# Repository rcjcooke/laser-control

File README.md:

# laser-control
Controller and Wi-fi enabler for Atomstack X20 Pro laser cutter, air assist and air filter

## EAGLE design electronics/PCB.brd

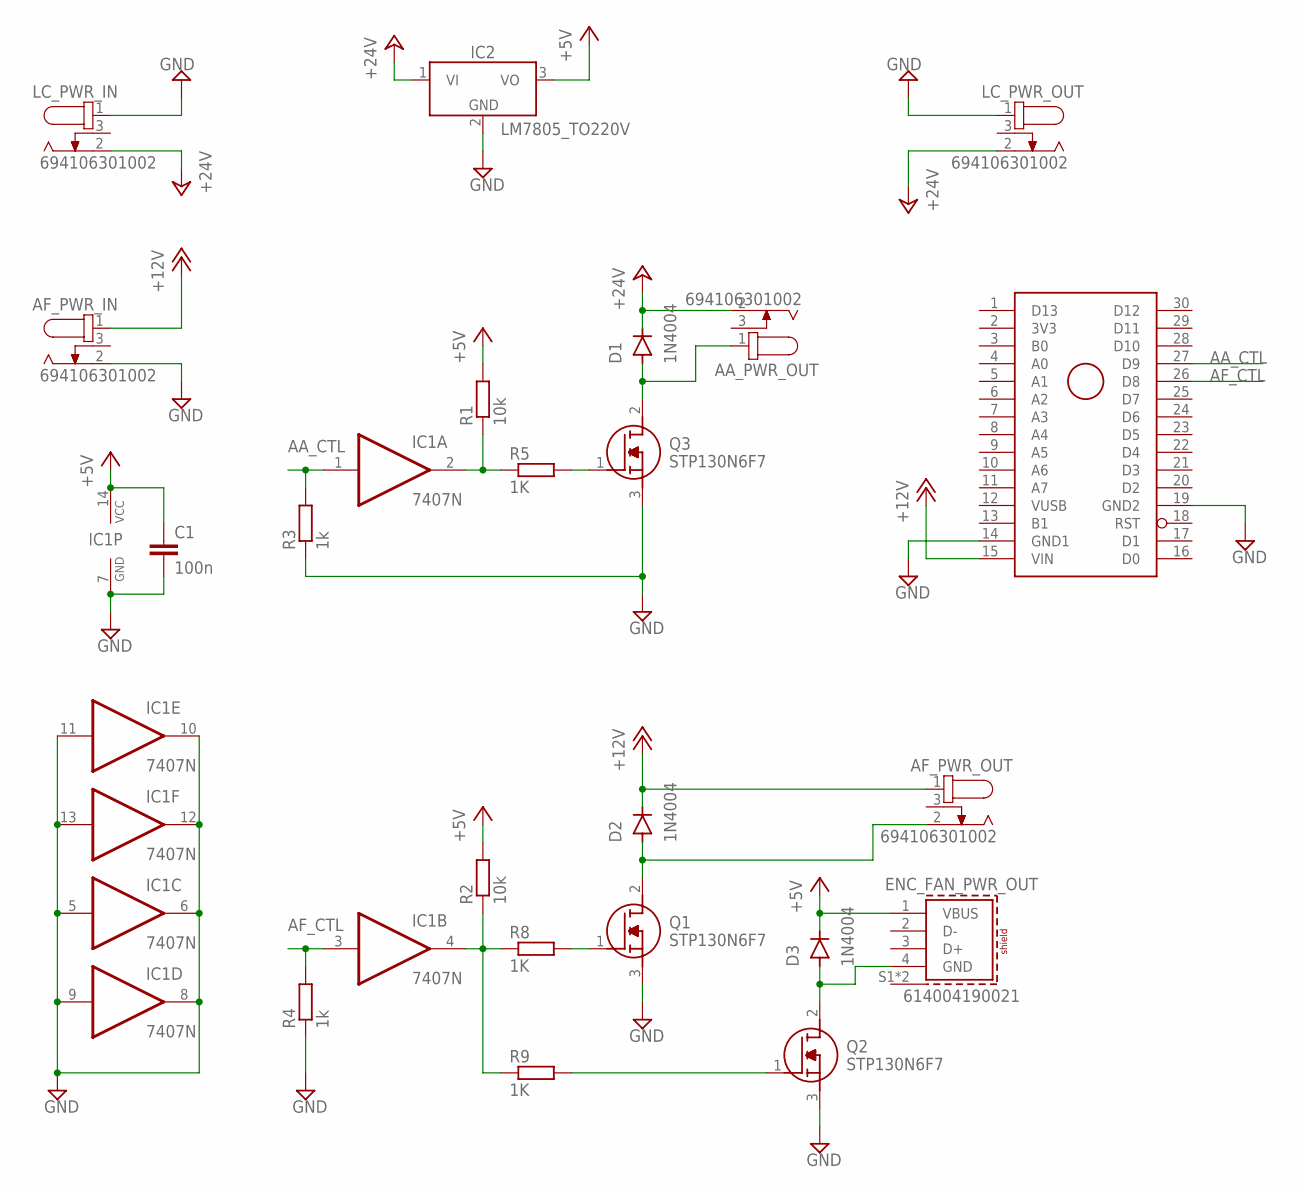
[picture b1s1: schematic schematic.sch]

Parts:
AA_PWR_OUT: 694106301002
AF_PWR_IN: 694106301002
AF_PWR_OUT: 694106301002
C1: 100n; C050-024X044
D1, D2, D3: 1N4004; DO-41
ENC_FAN_PWR_OUT: 614004190021
IC1: 7407N; DIL14
IC2: LM7805_TO220V; TO220V
LC_PWR_IN: 694106301002
LC_PWR_OUT: 694106301002
Q1, Q2, Q3: STP130N6F7; TO255P460X1020X2008-3P
R1, R2: 10k; 0204/7
R3, R4: 1k; 0204/7
R5, R8, R9: 1K; 0204/7
U$1: ARDUINO_NANO_ESP32; ARDUINO_NANO_ESP32_ON_HEADERS

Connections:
+5V: C1.1, D3.C, ENC_FAN_PWR_OUT.1 (VBUS), IC1.14 (VCC), IC2.3 (VO), R1.2, R2.2
+12V: AF_PWR_IN.1, AF_PWR_OUT.1, D2.C, U$1.15 (VIN)
+24V: AA_PWR_OUT.2, D1.C, IC2.1 (VI), LC_PWR_IN.2, LC_PWR_OUT.2
AA_CTL: IC1.1 (I), R3.2, U$1.27 (D9)
AF_CTL: IC1.3 (I), R4.2, U$1.26 (D8)
GND: AF_PWR_IN.2, C1.2, IC1.5 (I), IC1.6 (O), IC1.7 (GND), IC1.8 (O), IC1.9 (I), IC1.10 (O), IC1.11 (I), IC1.12 (O), IC1.13 (I), IC2.2 (GND), LC_PWR_IN.1, LC_PWR_OUT.1, Q1.3 (S), Q2.3 (S), Q3.3 (S), R3.1, R4.1, U$1.14 (GND1), U$1.19 (GND2)
unnamed: AF_PWR_OUT.2, D2.A, Q1.2 (D)
unnamed: Q2.1 (G), R9.2
unnamed: IC1.2 (O), R1.1, R5.1
unnamed: Q1.1 (G), R8.2
unnamed: Q3.1 (G), R5.2
unnamed: D3.A, ENC_FAN_PWR_OUT.4 (GND), Q2.2 (D)
unnamed: IC1.4 (O), R2.1, R8.1, R9.1
unnamed: AA_PWR_OUT.1, D1.A, Q3.2 (D)

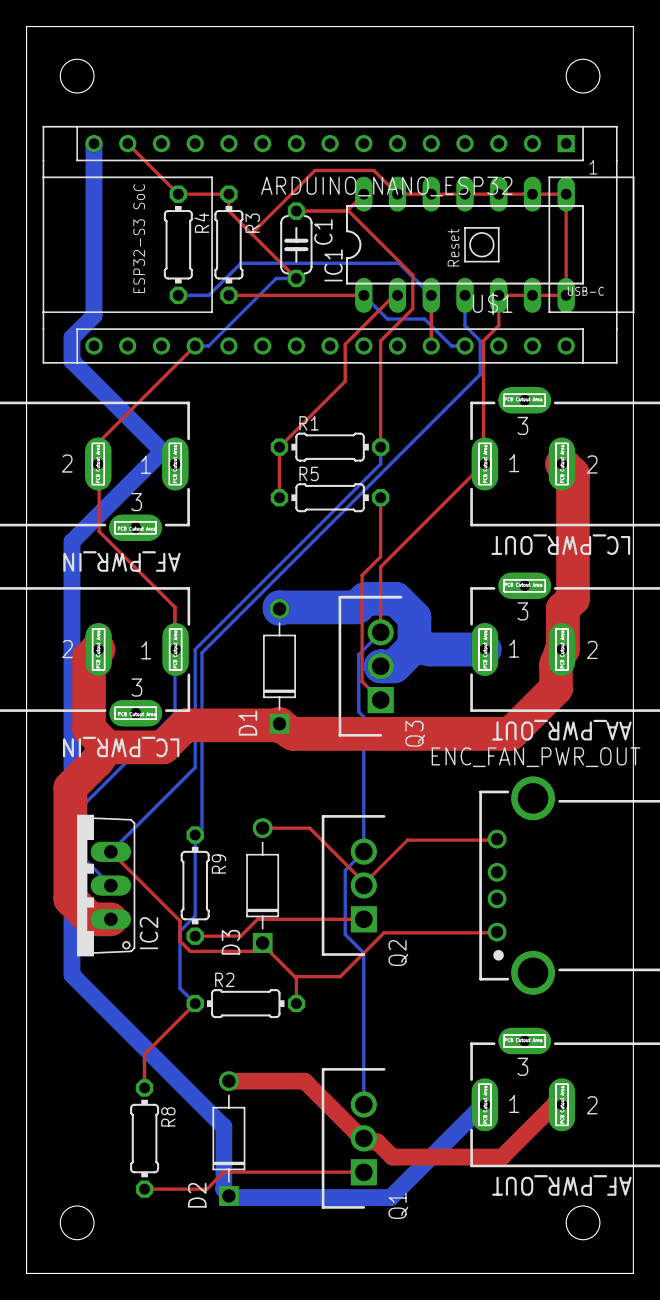
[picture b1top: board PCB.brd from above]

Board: 2 copper layers, 45.6 x 93.8 mm, 23 parts (0 on the bottom side), 14 nets.

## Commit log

2023-11-15 First cut
2023-11-15 Fixed spinner decleration bug
2023-11-19 Added startup status. Fixed bug in update spinner.

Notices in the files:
parts and their libraries:
Wurth_Connectors_WR-DC: Copyright: Würth Elektronik
